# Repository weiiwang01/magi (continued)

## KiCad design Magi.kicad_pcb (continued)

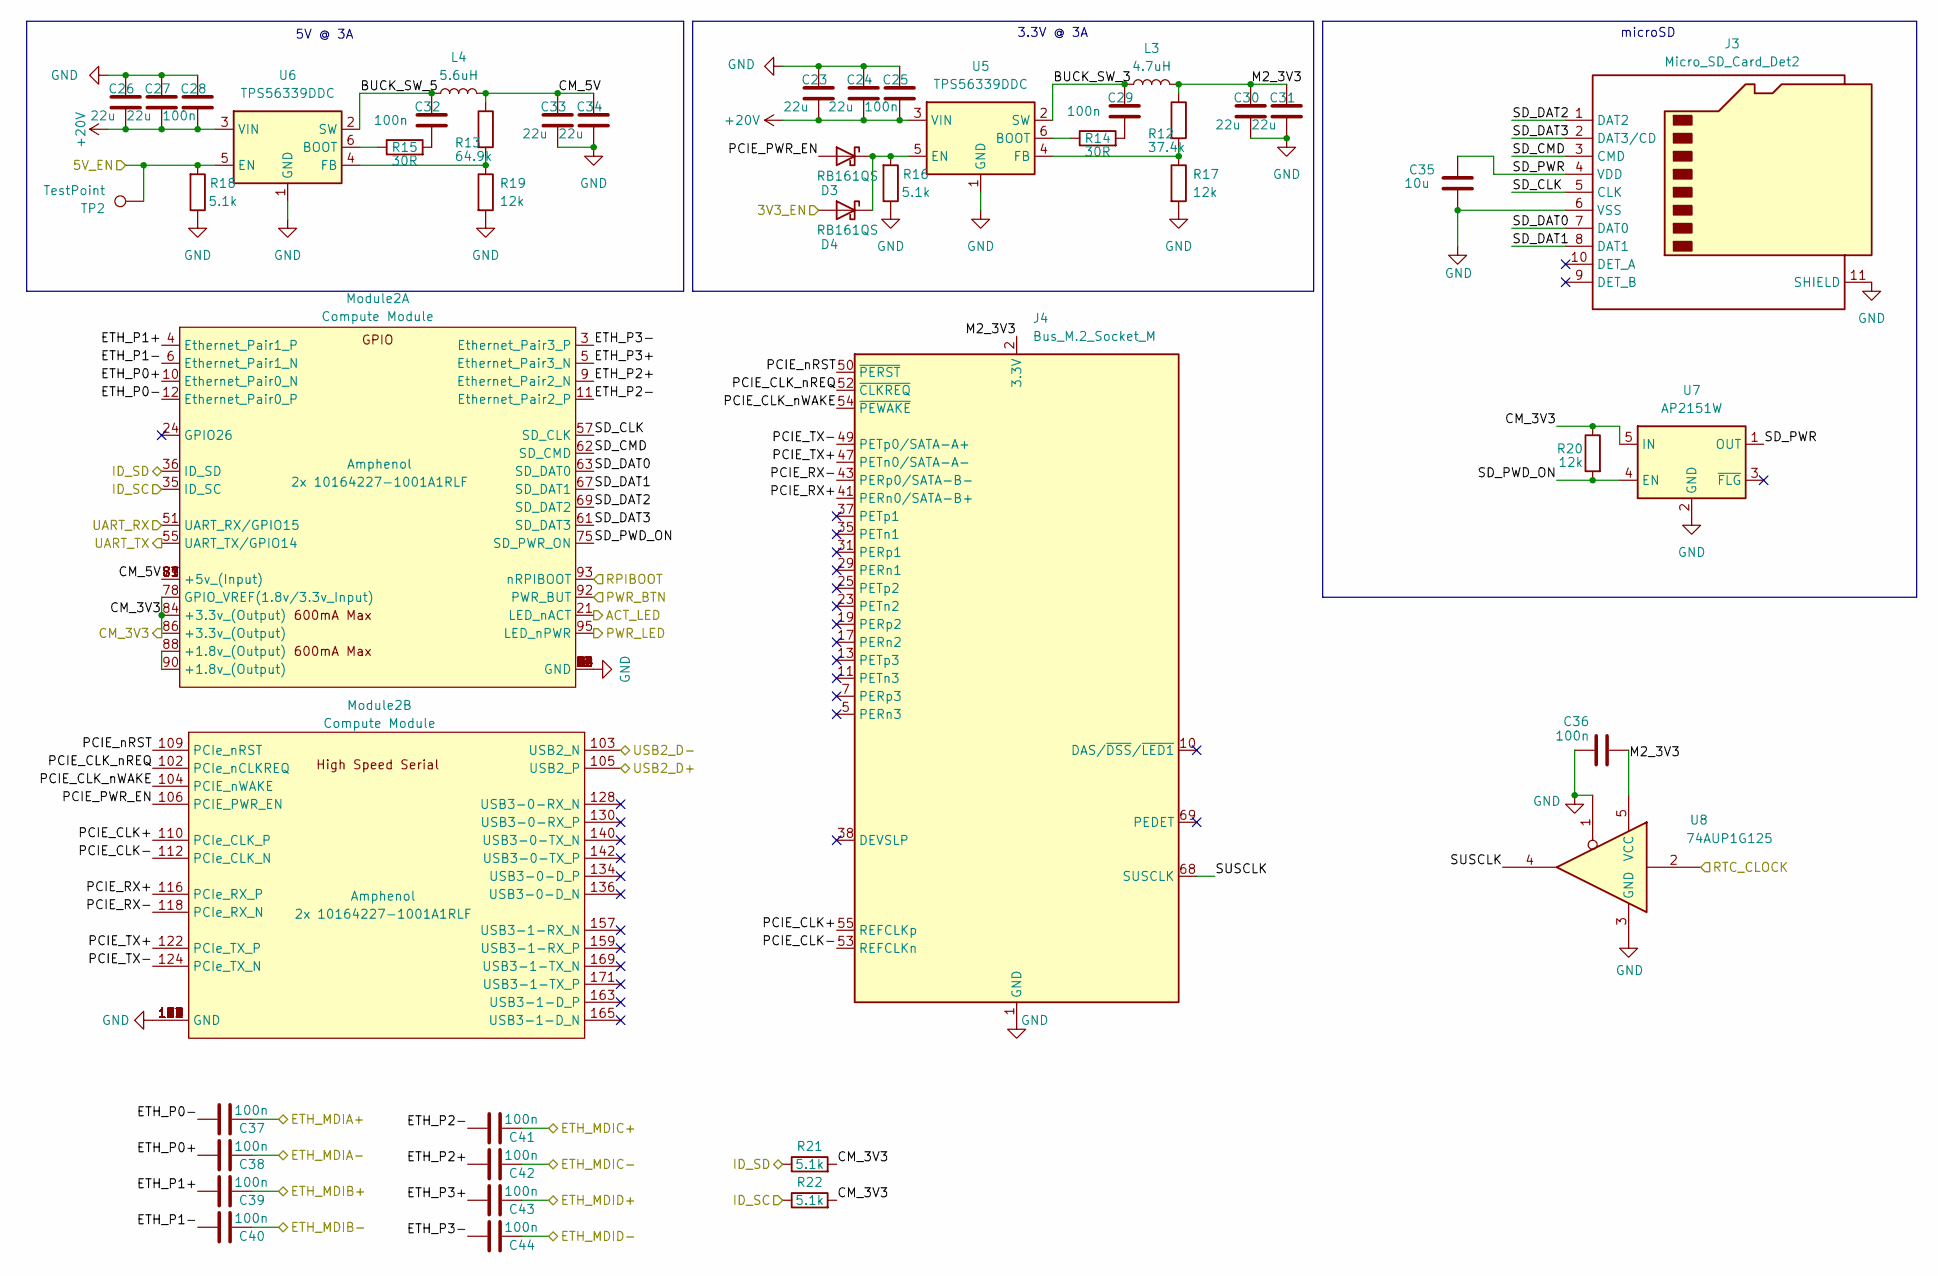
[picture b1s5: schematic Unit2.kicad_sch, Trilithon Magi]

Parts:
C23, C24, C26, C27, C30, C31, C33, C34: 22u; C_0805_2012Metric; MPN CL21A226MAQNNNE; LCSC C45783
C25, C28, C29, C32, C36, C37, C38, C39, C40, C41, C42, C43, C44: 100n; C_0402_1005Metric; MPN CL05B104KB54PNC; LCSC C307331
C35: 10u; C_0603_1608Metric; MPN CL10A106MA8NRNC; LCSC C96446
D3, D4: RB161QS; D_SOD-882; MPN RB161QS-40; LCSC C28646385
J3: Micro_SD_Card_Det2; SDCARD_MOLEX_503398-1892; MPN 5033981892; LCSC C428492
J4: Bus_M.2_Socket_M; CONN-SMD_APCI0146-P001A; MPN APCI0146-P001A; LCSC C841645
L3: 4.7uH; L_Changjiang_FTC404030S; MPN FTC404030S4R7MGCA; LCSC C39676083
L4: 5.6uH; L_Changjiang_FTC404030S; MPN FTC404030S5R6MBCA; LCSC C53436374
Module2: Compute Module; Raspberry-Pi-4-Compute-Module
R12: 37.4k; R_0402_1005Metric; MPN RC0402FR-0737K4L; LCSC C185422
R13: 64.9k; R_0402_1005Metric; MPN ERJ2RKF6492X; LCSC C416566
R14, R15: 30R; R_0402_1005Metric; MPN 0402WGF300JTCE; LCSC C270617
R16, R18, R21, R22: 5.1k; R_0402_1005Metric; MPN 0402WGF5101TCE; LCSC C25905
R17, R19, R20: 12k; R_0402_1005Metric; MPN 0402WGF1202TCE; LCSC C25752
TP2: TestPoint; TestPoint_Pad_D1.5mm
U5, U6: TPS56339DDC; SOT-23-6; MPN TPS56339DDCR; LCSC C2071106
U7: AP2151W; SOT-23-5; MPN AP2151WG-7; LCSC C110464
U8: 74AUP1G125; Texas_X2SON-5_0.8x0.8mm_P0.48mm; MPN SN74AUP1G125DPWR; LCSC C2861319

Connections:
+20V: C23.2, C24.2, C25.2, C26.2, C27.2, C28.2, U5.3 (VIN), U6.3 (VIN); also elsewhere on the board
/Controller/HUB_USB2_2_D+: Module2.103 (USB2_N); also elsewhere on the board
/Controller/HUB_USB2_2_D-: Module2.105 (USB2_P); also elsewhere on the board
/Controller/PA6_I2C3_SDA: Module2.36 (ID_SD), R21.1; also elsewhere on the board
/Controller/PA7_I2C3_SCL: Module2.35 (ID_SC), R22.1; also elsewhere on the board
/Controller/PB1: Module2.21 (LED_nACT); also elsewhere on the board
/Controller/PC4_USART1_TX: Module2.51 (UART_RX/GPIO15); also elsewhere on the board
/Controller/PC5_USART1_RX: Module2.55 (UART_TX/GPIO14); also elsewhere on the board
/Controller/PD4: D4.2 (A); also elsewhere on the board
/Controller/PE7: Module2.95 (LED_nPWR); also elsewhere on the board
/Controller/PE13: R18.2, TP2.1 (1_1), U6.5 (EN); also elsewhere on the board
/Controller/PF6: Module2.92 (PWR_BUT); also elsewhere on the board
/Controller/PF7: Module2.93 (nRPIBOOT); also elsewhere on the board
/Ethernet Switch/P1MDIA+: C39.1; also elsewhere on the board
/Ethernet Switch/P1MDIA-: C40.1; also elsewhere on the board
/Ethernet Switch/P1MDIB+: C38.1; also elsewhere on the board
/Ethernet Switch/P1MDIB-: C37.1; also elsewhere on the board
/Ethernet Switch/P1MDIC+: C44.1; also elsewhere on the board
/Ethernet Switch/P1MDIC-: C43.1; also elsewhere on the board
/Ethernet Switch/P1MDID+: C42.1; also elsewhere on the board
/Ethernet Switch/P1MDID-: C41.1; also elsewhere on the board
/LSCO: U8.2; also elsewhere on the board
/Unit 2/BUCK_SW_3: C29.1, L3.1, U5.2 (SW)
/Unit 2/BUCK_SW_5: C32.1, L4.1, U6.2 (SW)
/Unit 2/CM_3V3: Module2.78 (GPIO_VREF(1.8v/3.3v_Input)), Module2.84 (+3.3v_(Output)), Module2.86 (+3.3v_(Output)), R20.1, R21.2, R22.2, U7.5 (IN); also elsewhere on the board
/Unit 2/CM_5V: C33.1, C34.1, L4.2, Module2.77 (+5v_(Input)), Module2.79 (+5v_(Input)), Module2.81 (+5v_(Input)), Module2.83 (+5v_(Input)), Module2.85 (+5v_(Input)), Module2.87 (+5v_(Input)), R13.1
/Unit 2/ETH_P0+: C38.2, Module2.10 (Ethernet_Pair0_N)
/Unit 2/ETH_P0-: C37.2, Module2.12 (Ethernet_Pair0_P)
/Unit 2/ETH_P1+: C39.2, Module2.4 (Ethernet_Pair1_P)
/Unit 2/ETH_P1-: C40.2, Module2.6 (Ethernet_Pair1_N)
/Unit 2/ETH_P2+: C42.2, Module2.9 (Ethernet_Pair2_N)
/Unit 2/ETH_P2-: C41.2, Module2.11 (Ethernet_Pair2_P)
/Unit 2/ETH_P3+: C43.2, Module2.5 (Ethernet_Pair3_N)
/Unit 2/ETH_P3-: C44.2, Module2.3 (Ethernet_Pair3_P)
/Unit 2/M2_3V3: C30.1, C31.1, C36.2, J4.2 (3.3V), J4.4 (3.3V), J4.12 (3.3V), J4.14 (3.3V), J4.16 (3.3V), J4.18 (3.3V), J4.70 (3.3V), J4.72 (3.3V), J4.74 (3.3V), L3.2, R12.1, U8.5 (VCC)
/Unit 2/PCIE_CLK+: J4.55 (REFCLKp), Module2.110 (PCIe_CLK_P)
/Unit 2/PCIE_CLK-: J4.53 (REFCLKn), Module2.112 (PCIe_CLK_N)
/Unit 2/PCIE_CLK_nREQ: J4.52 (~CLKREQ), Module2.102 (PCIe_nCLKREQ)
/Unit 2/PCIE_CLK_nWAKE: J4.54 (~PEWAKE), Module2.104 (PCIE_nWAKE)
/Unit 2/PCIE_PWR_EN: D3.2 (A), Module2.106 (PCIE_PWR_EN)
/Unit 2/PCIE_RX+: J4.41 (PERn0/SATA-B+), Module2.116 (PCIe_RX_P)
/Unit 2/PCIE_RX-: J4.43 (PERp0/SATA-B-), Module2.118 (PCIe_RX_N)
/Unit 2/PCIE_TX+: J4.47 (PETn0/SATA-A-), Module2.122 (PCIe_TX_P)
/Unit 2/PCIE_TX-: J4.49 (PETp0/SATA-A+), Module2.124 (PCIe_TX_N)
/Unit 2/PCIE_nRST: J4.50 (~PERST), Module2.109 (PCIe_nRST)
/Unit 2/SD_CLK: J3.5 (CLK), Module2.57 (SD_CLK)
/Unit 2/SD_CMD: J3.3 (CMD), Module2.62 (SD_CMD)
/Unit 2/SD_DAT0: J3.7 (DAT0), Module2.63 (SD_DAT0)
/Unit 2/SD_DAT1: J3.8 (DAT1), Module2.67 (SD_DAT1)
/Unit 2/SD_DAT2: J3.1 (DAT2), Module2.69 (SD_DAT2)
/Unit 2/SD_DAT3: J3.2 (DAT3/CD), Module2.61 (SD_DAT3)
/Unit 2/SD_PWD_ON: Module2.75 (SD_PWR_ON), R20.2, U7.4 (EN)
/Unit 2/SD_PWR: C35.1, J3.4 (VDD), U7.1 (OUT)
/Unit 2/SUSCLK: J4.68 (SUSCLK), U8.4
GND: C23.1, C24.1, C25.1, C26.1, C27.1, C28.1, C30.2, C31.2, C33.2, C34.2, C35.2, C36.1, J3.6 (VSS), J3.11 (SHIELD), J4.1 (GND), J4.3 (GND), J4.9 (GND), J4.15 (GND), J4.21 (GND), J4.27 (GND), J4.33 (GND), J4.39 (GND), J4.45 (GND), J4.51 (GND), J4.57 (GND), J4.71 (GND), J4.73 (GND), J4.75 (GND), Module2.1 (GND), Module2.2 (GND), Module2.7 (GND), Module2.8 (GND), Module2.13 (GND), Module2.14 (GND), Module2.22 (GND), Module2.23 (GND), Module2.32 (GND), Module2.33 (GND), Module2.42 (GND), Module2.43 (GND), Module2.52 (GND), Module2.53 (GND), Module2.59 (GND), Module2.60 (GND), Module2.65 (GND), Module2.66 (GND), Module2.71 (GND), Module2.74 (GND), Module2.98 (GND), Module2.107 (GND), Module2.108 (GND), Module2.113 (GND), Module2.114 (GND), Module2.119 (GND), Module2.120 (GND), Module2.125 (GND), Module2.126 (GND), Module2.131 (GND), Module2.132 (GND), Module2.137 (GND), Module2.138 (GND), Module2.144 (GND), Module2.150 (GND), Module2.155 (GND), Module2.156 (GND), Module2.161 (GND), Module2.162 (GND), Module2.167 (GND), Module2.168 (GND), Module2.173 (GND), Module2.174 (GND), Module2.179 (GND), Module2.180 (GND), Module2.185 (GND), Module2.186 (GND), Module2.191 (GND), Module2.192 (GND), Module2.197 (GND), Module2.198 (GND), R16.1, R17.2, R18.1, R19.2, U5.1 (GND), U6.1 (GND), U7.2 (GND), U8.1, U8.3 (GND); also elsewhere on the board
unnamed: C29.2, R14.2
unnamed: C32.2, R15.2
unnamed: D3.1 (K), D4.1 (K), R16.2, U5.5 (EN)
unnamed: Module2.88 (+1.8v_(Output)), Module2.90 (+1.8v_(Output))
unnamed: R14.1, U5.6 (BOOT)
unnamed: R12.2, R17.1, U5.4 (FB)
unnamed: R15.1, U6.6 (BOOT)
unnamed: R13.2, R19.1, U6.4 (FB)

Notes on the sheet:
microSD
5V @ 3A
3.3V @ 3A

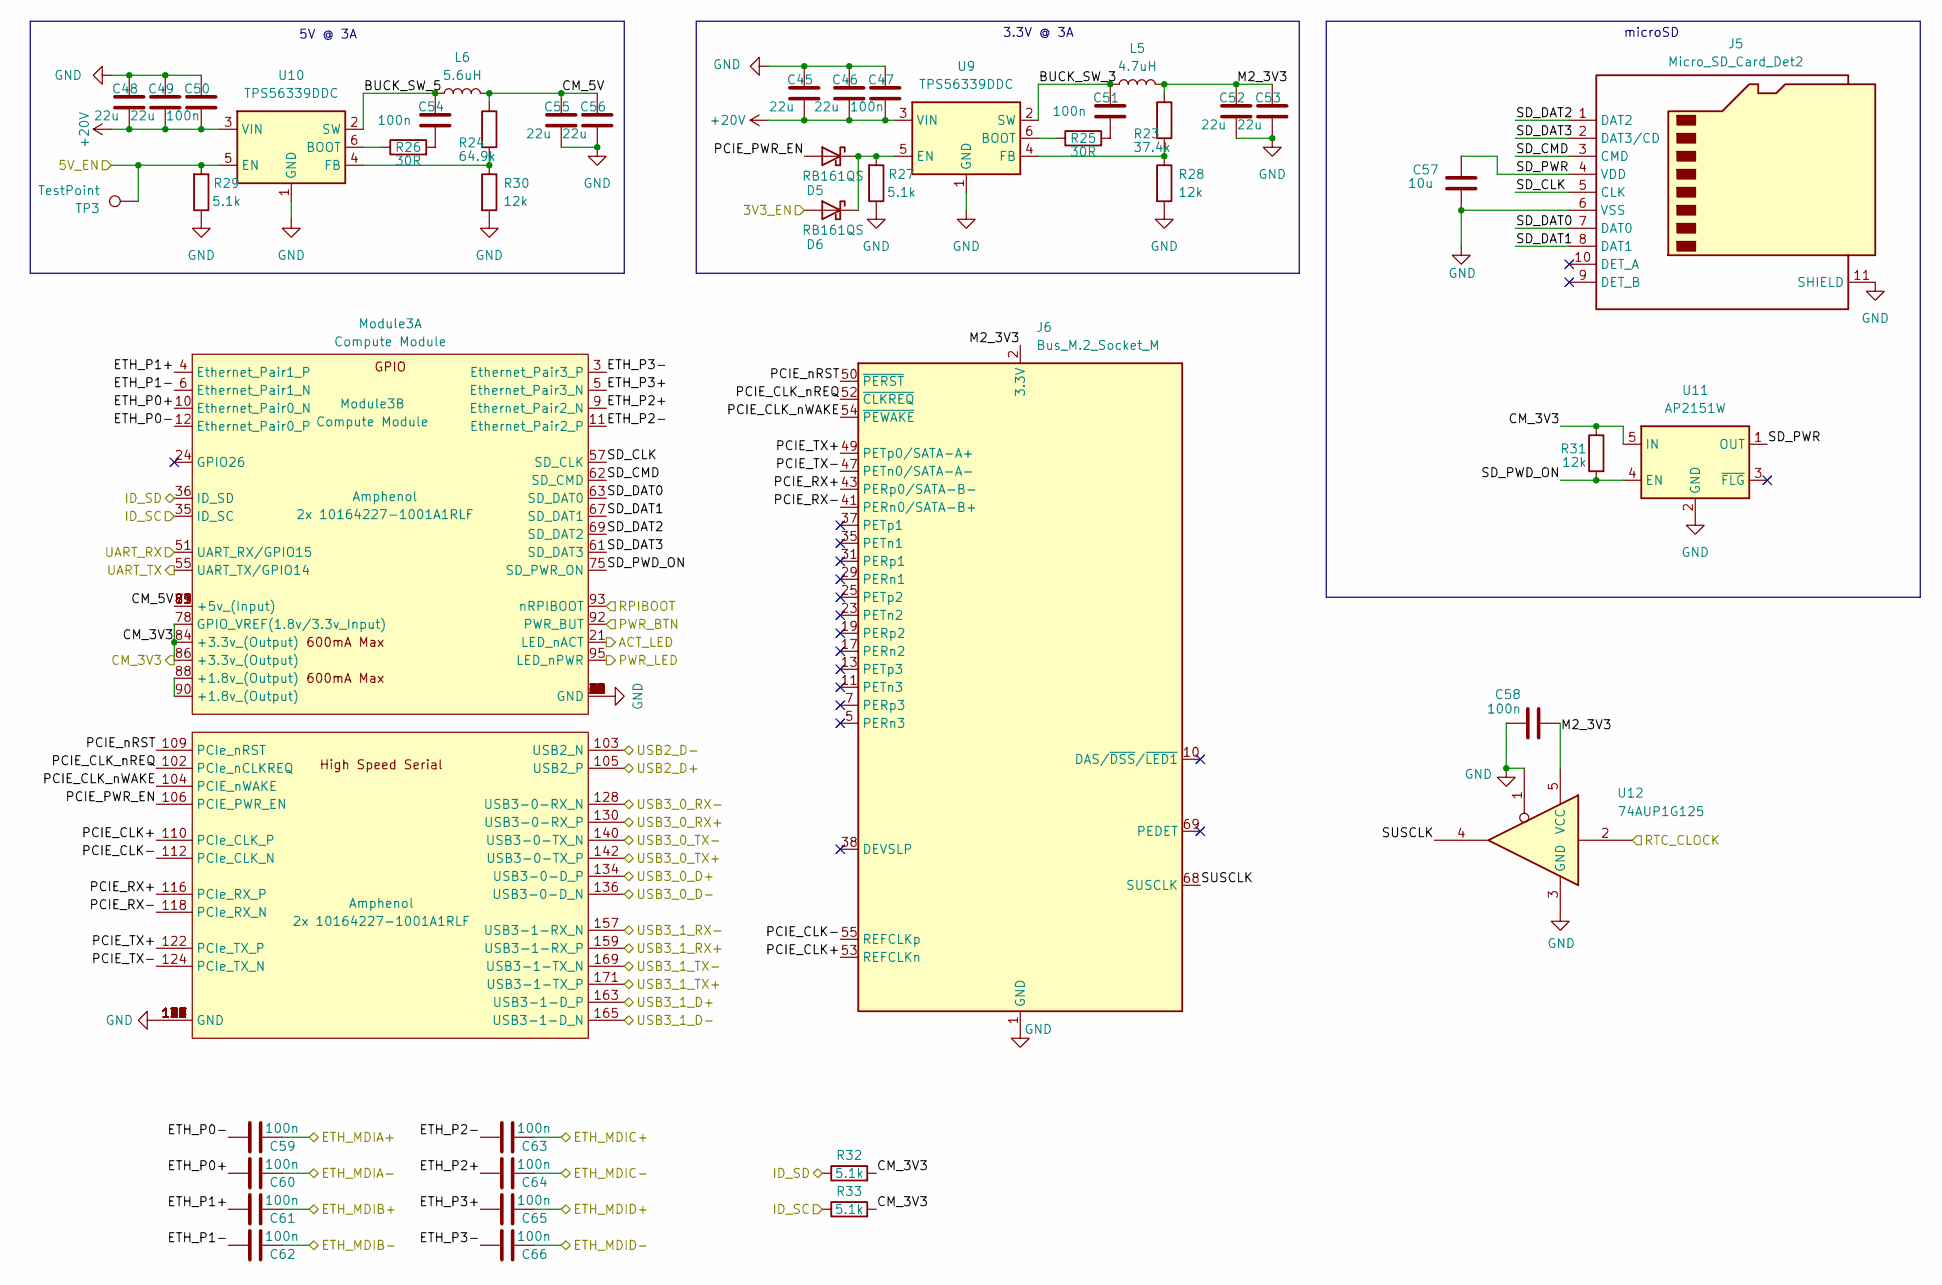
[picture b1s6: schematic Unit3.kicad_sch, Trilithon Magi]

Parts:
C45, C46, C48, C49, C52, C53, C55, C56: 22u; C_0805_2012Metric; MPN CL21A226MAQNNNE; LCSC C45783
C47, C50, C51, C54, C58, C59, C60, C61, C62, C63, C64, C65, C66: 100n; C_0402_1005Metric; MPN CL05B104KB54PNC; LCSC C307331
C57: 10u; C_0603_1608Metric; MPN CL10A106MA8NRNC; LCSC C96446
D5, D6: RB161QS; D_SOD-882; MPN RB161QS-40; LCSC C28646385
J5: Micro_SD_Card_Det2; SDCARD_MOLEX_503398-1892; MPN 5033981892; LCSC C428492
J6: Bus_M.2_Socket_M; CONN-SMD_APCI0146-P001A; MPN APCI0146-P001A; LCSC C841645
L5: 4.7uH; L_Changjiang_FTC404030S; MPN FTC404030S4R7MGCA; LCSC C39676083
L6: 5.6uH; L_Changjiang_FTC404030S; MPN FTC404030S5R6MBCA; LCSC C53436374
Module3: Compute Module; Raspberry-Pi-4-Compute-Module
R23: 37.4k; R_0402_1005Metric; MPN RC0402FR-0737K4L; LCSC C185422
R24: 64.9k; R_0402_1005Metric; MPN ERJ2RKF6492X; LCSC C416566
R25, R26: 30R; R_0402_1005Metric; MPN 0402WGF300JTCE; LCSC C270617
R27, R29, R32, R33: 5.1k; R_0402_1005Metric; MPN 0402WGF5101TCE; LCSC C25905
R28, R30, R31: 12k; R_0402_1005Metric; MPN 0402WGF1202TCE; LCSC C25752
TP3: TestPoint; TestPoint_Pad_D1.5mm
U9, U10: TPS56339DDC; SOT-23-6; MPN TPS56339DDCR; LCSC C2071106
U11: AP2151W; SOT-23-5; MPN AP2151WG-7; LCSC C110464
U12: 74AUP1G125; Texas_X2SON-5_0.8x0.8mm_P0.48mm; MPN SN74AUP1G125DPWR; LCSC C2861319

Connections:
+20V: C45.2, C46.2, C47.2, C48.2, C49.2, C50.2, U9.3 (VIN), U10.3 (VIN); also elsewhere on the board
/Controller/HUB_USB2_3_D+: Module3.105 (USB2_P); also elsewhere on the board
/Controller/HUB_USB2_3_D-: Module3.103 (USB2_N); also elsewhere on the board
/Controller/PB13_I2C2_SCL: Module3.35 (ID_SC), R33.1; also elsewhere on the board
/Controller/PB14_I2C2_SDA: Module3.36 (ID_SD), R32.1; also elsewhere on the board
/Controller/PD8_USART3_TX: Module3.51 (UART_RX/GPIO15); also elsewhere on the board
/Controller/PD9_USART3_RX: Module3.55 (UART_TX/GPIO14); also elsewhere on the board
/Controller/PD13: R29.2, TP3.1 (1_1), U10.5 (EN); also elsewhere on the board
/Controller/PD14: Module3.92 (PWR_BUT); also elsewhere on the board
/Controller/PD15: Module3.95 (LED_nPWR); also elsewhere on the board
/Controller/PE14: D6.2 (A); also elsewhere on the board
/Controller/PE15: Module3.21 (LED_nACT); also elsewhere on the board
/Controller/PF8: Module3.93 (nRPIBOOT); also elsewhere on the board
/Ethernet Switch/P2MDIA+: C62.1; also elsewhere on the board
/Ethernet Switch/P2MDIA-: C61.1; also elsewhere on the board
/Ethernet Switch/P2MDIB+: C60.1; also elsewhere on the board
/Ethernet Switch/P2MDIB-: C59.1; also elsewhere on the board
/Ethernet Switch/P2MDIC+: C66.1; also elsewhere on the board
/Ethernet Switch/P2MDIC-: C65.1; also elsewhere on the board
/Ethernet Switch/P2MDID+: C63.1; also elsewhere on the board
/Ethernet Switch/P2MDID-: C64.1; also elsewhere on the board
/Interconnect/USB_D+: Module3.134 (USB3-0-D_P); also elsewhere on the board
/Interconnect/USB_D-: Module3.136 (USB3-0-D_N); also elsewhere on the board
/Interconnect/USB_SS_RX+: Module3.128 (USB3-0-RX_N); also elsewhere on the board
/Interconnect/USB_SS_RX-: Module3.130 (USB3-0-RX_P); also elsewhere on the board
/Interconnect/USB_SS_TX+: Module3.142 (USB3-0-TX_P); also elsewhere on the board
/Interconnect/USB_SS_TX-: Module3.140 (USB3-0-TX_N); also elsewhere on the board
/LSCO: U12.2; also elsewhere on the board
/USB/USB_D+: Module3.163 (USB3-1-D_P); also elsewhere on the board
/USB/USB_D-: Module3.165 (USB3-1-D_N); also elsewhere on the board
/USB/USB_SS_RX+: Module3.159 (USB3-1-RX_P); also elsewhere on the board
/USB/USB_SS_RX-: Module3.157 (USB3-1-RX_N); also elsewhere on the board
/USB/USB_SS_TX+: Module3.171 (USB3-1-TX_P); also elsewhere on the board
/USB/USB_SS_TX-: Module3.169 (USB3-1-TX_N); also elsewhere on the board
/Unit 3/BUCK_SW_3: C51.1, L5.1, U9.2 (SW)
/Unit 3/BUCK_SW_5: C54.1, L6.1, U10.2 (SW)
/Unit 3/CM_3V3: Module3.78 (GPIO_VREF(1.8v/3.3v_Input)), Module3.84 (+3.3v_(Output)), Module3.86 (+3.3v_(Output)), R31.1, R32.2, R33.2, U11.5 (IN); also elsewhere on the board
/Unit 3/CM_5V: C55.1, C56.1, L6.2, Module3.77 (+5v_(Input)), Module3.79 (+5v_(Input)), Module3.81 (+5v_(Input)), Module3.83 (+5v_(Input)), Module3.85 (+5v_(Input)), Module3.87 (+5v_(Input)), R24.1
/Unit 3/ETH_P0+: C60.2, Module3.10 (Ethernet_Pair0_N)
/Unit 3/ETH_P0-: C59.2, Module3.12 (Ethernet_Pair0_P)
/Unit 3/ETH_P1+: C61.2, Module3.4 (Ethernet_Pair1_P)
/Unit 3/ETH_P1-: C62.2, Module3.6 (Ethernet_Pair1_N)
/Unit 3/ETH_P2+: C64.2, Module3.9 (Ethernet_Pair2_N)
/Unit 3/ETH_P2-: C63.2, Module3.11 (Ethernet_Pair2_P)
/Unit 3/ETH_P3+: C65.2, Module3.5 (Ethernet_Pair3_N)
/Unit 3/ETH_P3-: C66.2, Module3.3 (Ethernet_Pair3_P)
/Unit 3/M2_3V3: C52.1, C53.1, C58.2, J6.2 (3.3V), J6.4 (3.3V), J6.12 (3.3V), J6.14 (3.3V), J6.16 (3.3V), J6.18 (3.3V), J6.70 (3.3V), J6.72 (3.3V), J6.74 (3.3V), L5.2, R23.1, U12.5 (VCC)
/Unit 3/PCIE_CLK+: J6.53 (REFCLKn), Module3.110 (PCIe_CLK_P)
/Unit 3/PCIE_CLK-: J6.55 (REFCLKp), Module3.112 (PCIe_CLK_N)
/Unit 3/PCIE_CLK_nREQ: J6.52 (~CLKREQ), Module3.102 (PCIe_nCLKREQ)
/Unit 3/PCIE_CLK_nWAKE: J6.54 (~PEWAKE), Module3.104 (PCIE_nWAKE)
/Unit 3/PCIE_PWR_EN: D5.2 (A), Module3.106 (PCIE_PWR_EN)
/Unit 3/PCIE_RX+: J6.43 (PERp0/SATA-B-), Module3.116 (PCIe_RX_P)
/Unit 3/PCIE_RX-: J6.41 (PERn0/SATA-B+), Module3.118 (PCIe_RX_N)
/Unit 3/PCIE_TX+: J6.49 (PETp0/SATA-A+), Module3.122 (PCIe_TX_P)
/Unit 3/PCIE_TX-: J6.47 (PETn0/SATA-A-), Module3.124 (PCIe_TX_N)
/Unit 3/PCIE_nRST: J6.50 (~PERST), Module3.109 (PCIe_nRST)
/Unit 3/SD_CLK: J5.5 (CLK), Module3.57 (SD_CLK)
/Unit 3/SD_CMD: J5.3 (CMD), Module3.62 (SD_CMD)
/Unit 3/SD_DAT0: J5.7 (DAT0), Module3.63 (SD_DAT0)
/Unit 3/SD_DAT1: J5.8 (DAT1), Module3.67 (SD_DAT1)
/Unit 3/SD_DAT2: J5.1 (DAT2), Module3.69 (SD_DAT2)
/Unit 3/SD_DAT3: J5.2 (DAT3/CD), Module3.61 (SD_DAT3)
/Unit 3/SD_PWD_ON: Module3.75 (SD_PWR_ON), R31.2, U11.4 (EN)
/Unit 3/SD_PWR: C57.1, J5.4 (VDD), U11.1 (OUT)
/Unit 3/SUSCLK: J6.68 (SUSCLK), U12.4
GND: C45.1, C46.1, C47.1, C48.1, C49.1, C50.1, C52.2, C53.2, C55.2, C56.2, C57.2, C58.1, J5.6 (VSS), J5.11 (SHIELD), J6.1 (GND), J6.3 (GND), J6.9 (GND), J6.15 (GND), J6.21 (GND), J6.27 (GND), J6.33 (GND), J6.39 (GND), J6.45 (GND), J6.51 (GND), J6.57 (GND), J6.71 (GND), J6.73 (GND), J6.75 (GND), Module3.1 (GND), Module3.2 (GND), Module3.7 (GND), Module3.8 (GND), Module3.13 (GND), Module3.14 (GND), Module3.22 (GND), Module3.23 (GND), Module3.32 (GND), Module3.33 (GND), Module3.42 (GND), Module3.43 (GND), Module3.52 (GND), Module3.53 (GND), Module3.56 (GPIO3), Module3.58 (GPIO2), Module3.59 (GND), Module3.60 (GND), Module3.65 (GND), Module3.66 (GND), Module3.71 (GND), Module3.74 (GND), Module3.98 (GND), Module3.107 (GND), Module3.108 (GND), Module3.113 (GND), Module3.114 (GND), Module3.119 (GND), Module3.120 (GND), Module3.125 (GND), Module3.126 (GND), Module3.131 (GND), Module3.132 (GND), Module3.137 (GND), Module3.138 (GND), Module3.144 (GND), Module3.150 (GND), Module3.155 (GND), Module3.156 (GND), Module3.161 (GND), Module3.162 (GND), Module3.167 (GND), Module3.168 (GND), Module3.173 (GND), Module3.174 (GND), Module3.179 (GND), Module3.180 (GND), Module3.185 (GND), Module3.186 (GND), Module3.191 (GND), Module3.192 (GND), Module3.197 (GND), Module3.198 (GND), R27.1, R28.2, R29.1, R30.2, U9.1 (GND), U10.1 (GND), U11.2 (GND), U12.1, U12.3 (GND); also elsewhere on the board
unnamed: C51.2, R25.2
unnamed: C54.2, R26.2
unnamed: D5.1 (K), D6.1 (K), R27.2, U9.5 (EN)
unnamed: Module3.88 (+1.8v_(Output)), Module3.90 (+1.8v_(Output))
unnamed: R25.1, U9.6 (BOOT)
unnamed: R23.2, R28.1, U9.4 (FB)
unnamed: R26.1, U10.6 (BOOT)
unnamed: R24.2, R30.1, U10.4 (FB)

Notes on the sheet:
microSD
3.3V @ 3A
5V @ 3A

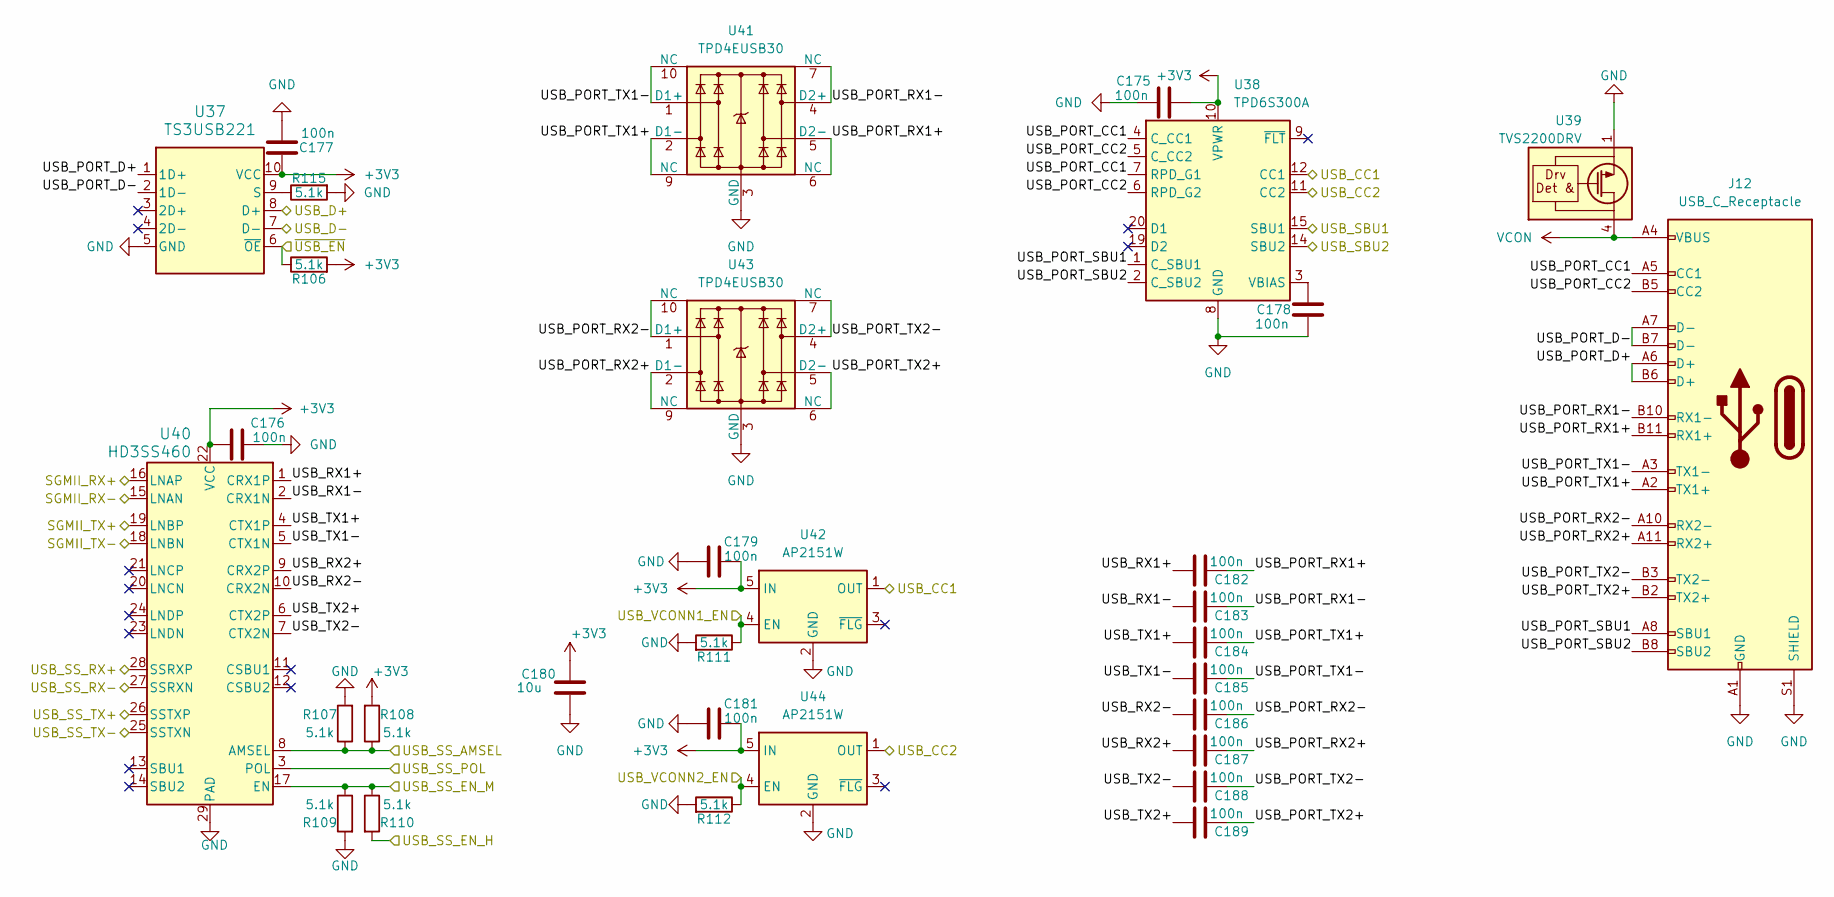
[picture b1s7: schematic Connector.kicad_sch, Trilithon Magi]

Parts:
C175, C176, C177, C178, C179, C181, C182, C183, C184, C185, C186, C187, C188, C189: 100n; C_0402_1005Metric; MPN CL05B104KB54PNC; LCSC C307331
C180: 10u; C_0603_1608Metric; MPN CL10A106MA8NRNC; LCSC C96446
J12: USB_C_Receptacle; USB-C-SMD_TYPE-C-GT-USB-7007C; MPN GT-USB-9007A; LCSC C48533148
R106, R107, R108, R109, R110, R111, R112, R115: 5.1k; R_0402_1005Metric; MPN 0402WGF5101TCE; LCSC C25905
U37: TS3USB221; Texas_UQFN-10_1.5x2mm_P0.5mm; MPN TS3USB221ARSER; LCSC C128396
U38: TPD6S300A; WQFN-20-1EP_3x3mm_P0.4mm_EP1.7x1.7mm_ThermalVias; MPN TPD6S300A; LCSC C2876380
U39: TVS2200DRV; WSON-6-1EP_2x2mm_P0.65mm_EP1x1.6mm; MPN TVS2200DRVR; LCSC C523793
U40: HD3SS460; WQFN-28-1EP_3.5x5.5mm_P0.5mm_EP2.05x4.05mm_ThermalVias_Sing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; MPN HD3SS460RHRT; LCSC C2150882
U41, U43: TPD4EUSB30; USON-10_2.5x1.0mm_P0.5mm; MPN TPD4EUSB30DQAR; LCSC C90627
U42, U44: AP2151W; SOT-23-5; MPN AP2151WG-7; LCSC C110464

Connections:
+3V3: C175.1, C176.1, C177.1, C179.1, C180.1, C181.1, R106.2, R108.2, U37.10 (VCC), U38.10 (VPWR), U40.22 (VCC), U42.5 (IN), U44.5 (IN); also elsewhere on the board
/Controller/PA15: R112.1, U44.4 (EN); also elsewhere on the board
/Controller/PC1: R106.1, U37.6 (~OE); also elsewhere on the board
/Controller/PC8: R111.1, U42.4 (EN); also elsewhere on the board
/Controller/PC13: U40.3 (POL); also elsewhere on the board
/Controller/PD5_USART2_TX: U38.14 (SBU2); also elsewhere on the board
/Controller/PD6_USART2_RX: U38.15 (SBU1); also elsewhere on the board
/Controller/PF0: R107.1, R108.1, U40.8 (AMSEL); also elsewhere on the board
/Controller/PF4: R109.1, R110.1, U40.17 (EN); also elsewhere on the board
/Controller/PF5: R110.2; also elsewhere on the board
/Controller/UCPD2_CC1: U38.12 (CC1), U42.1 (OUT); also elsewhere on the board
/Controller/UCPD2_CC2: U38.11 (CC2), U44.1 (OUT); also elsewhere on the board
/Ethernet Switch/SGMII_RX+: U40.16 (LNAP); also elsewhere on the board
/Ethernet Switch/SGMII_RX-: U40.15 (LNAN); also elsewhere on the board
/Ethernet Switch/SGMII_TX+: U40.19 (LNBP); also elsewhere on the board
/Ethernet Switch/SGMII_TX-: U40.18 (LNBN); also elsewhere on the board
/Interconnect/USB_D+: U37.8 (D+); also elsewhere on the board
/Interconnect/USB_D-: U37.7 (D-); also elsewhere on the board
/Interconnect/USB_PORT_CC1: J12.A5 (CC1), U38.4 (C_CC1), U38.7 (RPD_G1)
/Interconnect/USB_PORT_CC2: J12.B5 (CC2), U38.5 (C_CC2), U38.6 (RPD_G2)
/Interconnect/USB_PORT_D+: J12.A6 (D+), J12.B6 (D+), U37.1 (1D+)
/Interconnect/USB_PORT_D-: J12.A7 (D-), J12.B7 (D-), U37.2 (1D-)
/Interconnect/USB_PORT_RX1+: C182.1, J12.B11 (RX1+), U41.5 (D2-), U41.6 (NC)
/Interconnect/USB_PORT_RX1-: C183.1, J12.B10 (RX1-), U41.4 (D2+), U41.7 (NC)
/Interconnect/USB_PORT_RX2+: C187.1, J12.A11 (RX2+), U43.2 (D1-), U43.9 (NC)
/Interconnect/USB_PORT_RX2-: C186.1, J12.A10 (RX2-), U43.1 (D1+), U43.10 (NC)
/Interconnect/USB_PORT_SBU1: J12.A8 (SBU1), U38.1 (C_SBU1)
/Interconnect/USB_PORT_SBU2: J12.B8 (SBU2), U38.2 (C_SBU2)
/Interconnect/USB_PORT_TX1+: C184.1, J12.A2 (TX1+), U41.2 (D1-), U41.9 (NC)
/Interconnect/USB_PORT_TX1-: C185.1, J12.A3 (TX1-), U41.1 (D1+), U41.10 (NC)
/Interconnect/USB_PORT_TX2+: C189.1, J12.B2 (TX2+), U43.5 (D2-), U43.6 (NC)
/Interconnect/USB_PORT_TX2-: C188.1, J12.B3 (TX2-), U43.4 (D2+), U43.7 (NC)
/Interconnect/USB_RX1+: C182.2, U40.1 (CRX1P)
/Interconnect/USB_RX1-: C183.2, U40.2 (CRX1N)
/Interconnect/USB_RX2+: C187.2, U40.9 (CRX2P)
/Interconnect/USB_RX2-: C186.2, U40.10 (CRX2N)
/Interconnect/USB_SS_RX+: U40.28 (SSRXP); also elsewhere on the board
/Interconnect/USB_SS_RX-: U40.27 (SSRXN); also elsewhere on the board
/Interconnect/USB_SS_TX+: U40.26 (SSTXP); also elsewhere on the board
/Interconnect/USB_SS_TX-: U40.25 (SSTXN); also elsewhere on the board
/Interconnect/USB_TX1+: C184.2, U40.4 (CTX1P)
/Interconnect/USB_TX1-: C185.2, U40.5 (CTX1N)
/Interconnect/USB_TX2+: C189.2, U40.6 (CTX2P)
/Interconnect/USB_TX2-: C188.2, U40.7 (CTX2N)
GND: C175.2, C176.2, C177.2, C178.2, C179.2, C180.2, C181.2, J12.A1 (GND), J12.A12 (GND), J12.B1 (GND), J12.B12 (GND), J12.S1 (SHIELD), R107.2, R109.2, R111.2, R112.2, R115.2, U37.5 (GND), U38.8 (GND), U38.13 (GND), U38.16 (GND), U38.17 (GND), U38.18 (GND), U38.21 (GND), U39.1 (GND), U39.2 (GND), U39.3 (GND), U39.7 (GND), U40.29 (PAD), U41.3 (GND), U41.8 (GND), U42.2 (GND), U43.3 (GND), U43.8 (GND), U44.2 (GND); also elsewhere on the board
unnamed: R115.1, U37.9 (S)
unnamed: C178.1, U38.3 (VBIAS)
VCON: J12.A4 (VBUS), J12.A9 (VBUS), J12.B4 (VBUS), J12.B9 (VBUS), U39.4 (IN), U39.5 (IN), U39.6 (IN); also elsewhere on the board
